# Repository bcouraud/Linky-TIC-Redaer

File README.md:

# Linky-TIC-Reader
This repository stores the files to reproduce a Linky TIC Reader.
The architecture includes:
- A communication moduel, i.e. a Wemo D1 Lite that can be programmed from the arduino IDE
- A power supply that consists of a large capacitor and a microchip PIC 12f1840 micrcontroller to switch on/off the communication module if there is not enough energy in the capacitor. 
- a TIC demodulation circuit

The current folder includes:
- The PCB files to reproduce it. They can be opened from KICad free software
- The arduino code for the wemo module to operate: wake up - read the TIC information - read the capacitor voltage - if there is enough energy in the capcitor, send the data in https.
- The C code for the microchip PIC 12F1840 that was developed in MPLAB IDE, and programmed into the microcontroller using a PicKit 2 directly plugged into the dedicated connectors in the PCB

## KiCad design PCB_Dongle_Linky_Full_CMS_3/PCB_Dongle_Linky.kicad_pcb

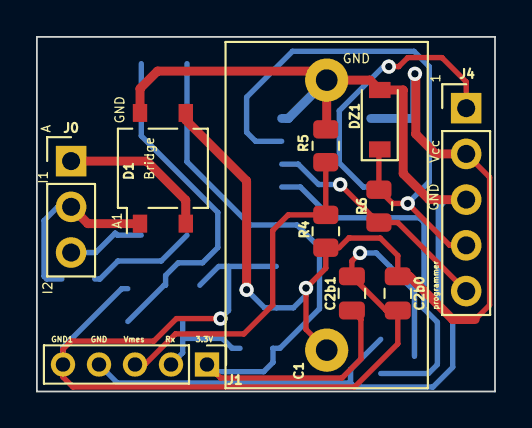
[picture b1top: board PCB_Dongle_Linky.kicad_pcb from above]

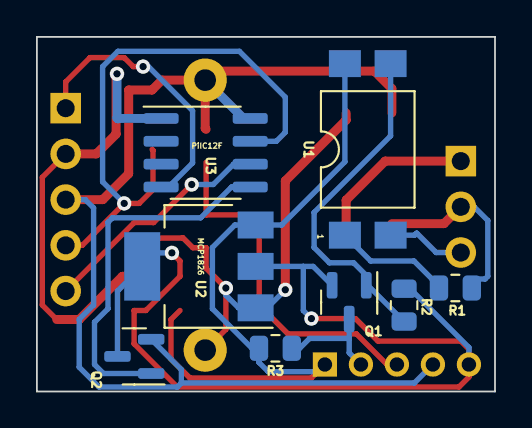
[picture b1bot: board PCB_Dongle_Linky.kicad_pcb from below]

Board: 2 copper layers, 25.5 x 19.7 mm, 19 parts (8 on the bottom side), 15 nets.

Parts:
C1: C; C_Rect_L19.0mm_W11.0mm_P15.00mm_MKS4
C2b0, C2b1: C; C_0805_2012Metric
D1: MB6S; TO-269AA
DZ1: BAT43W-V; D_SOD-123
J0: Linky; PinHeader_1x03_P2.54mm_Vertical
J1: ESP; PinHeader_1x05_P2.00mm_Vertical
J4: program; PinHeader_1x05_P2.54mm_Vertical
Q1: BS170F; SOT-23
Q2: IRLML6244; SOT-23
R1, R2, R3, R4, R5, R6: R_US; R_0805_2012Metric
U1: SFH6206-2T; SMDIP-4_W9.53mm_Clearance8mm
U2: MCP1825s33; SOT-223-3_TabPin2
U3: PIC12F1840-IP; SOIC-8_3.9x4.9mm_P1.27mm

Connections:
+3.3V: C2b1.1, J1.1, R3.2, U1.4, U2.3 (VO)
A: D1.2, J0.1
GND: C1.2, D1.4 (-), DZ1.2 (A), J1.4, J4.3, Q2.2 (S), R5.1, U3.8 (VSS)
GND1: C2b0.2, C2b1.2, J1.5, Q1.2 (S), Q2.3 (D), R2.1, U2.2 (GND)
I1: D1.1, J0.2, R1.1
I2: J0.3, U1.2
unnamed: DZ1.1 (K), J4.4, R6.1, U3.7 (RA0)
unnamed: J1.2, Q1.3 (D), R3.1
unnamed: J1.3, R4.1, R5.2
unnamed: J4.1, U3.4 (RA3)
unnamed: J4.5, R6.2, U3.6 (RA1)
unnamed: Q1.1 (G), R2.2, U1.3
unnamed: Q2.1 (G), U3.5 (RA2)
unnamed: R1.2, U1.1
VCC: C1.1, C2b0.1, D1.3 (+), J4.2, R4.2, U2.1 (VI), U3.1 (VDD)

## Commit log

2023-06-03 Rename main_original.c to PIC_main_original.c
2023-06-03 Rename AccessPoint.ino to AccessPoint_for_reference.ino
2023-12-29 Add PCB and arduino Code revised to the main branch
2024-09-25 full update of this directory
2024-09-25 change Readme
2024-09-25 change file wemo
